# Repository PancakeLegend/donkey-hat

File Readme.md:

#CCHS dingo-hat

This is the readme.
---

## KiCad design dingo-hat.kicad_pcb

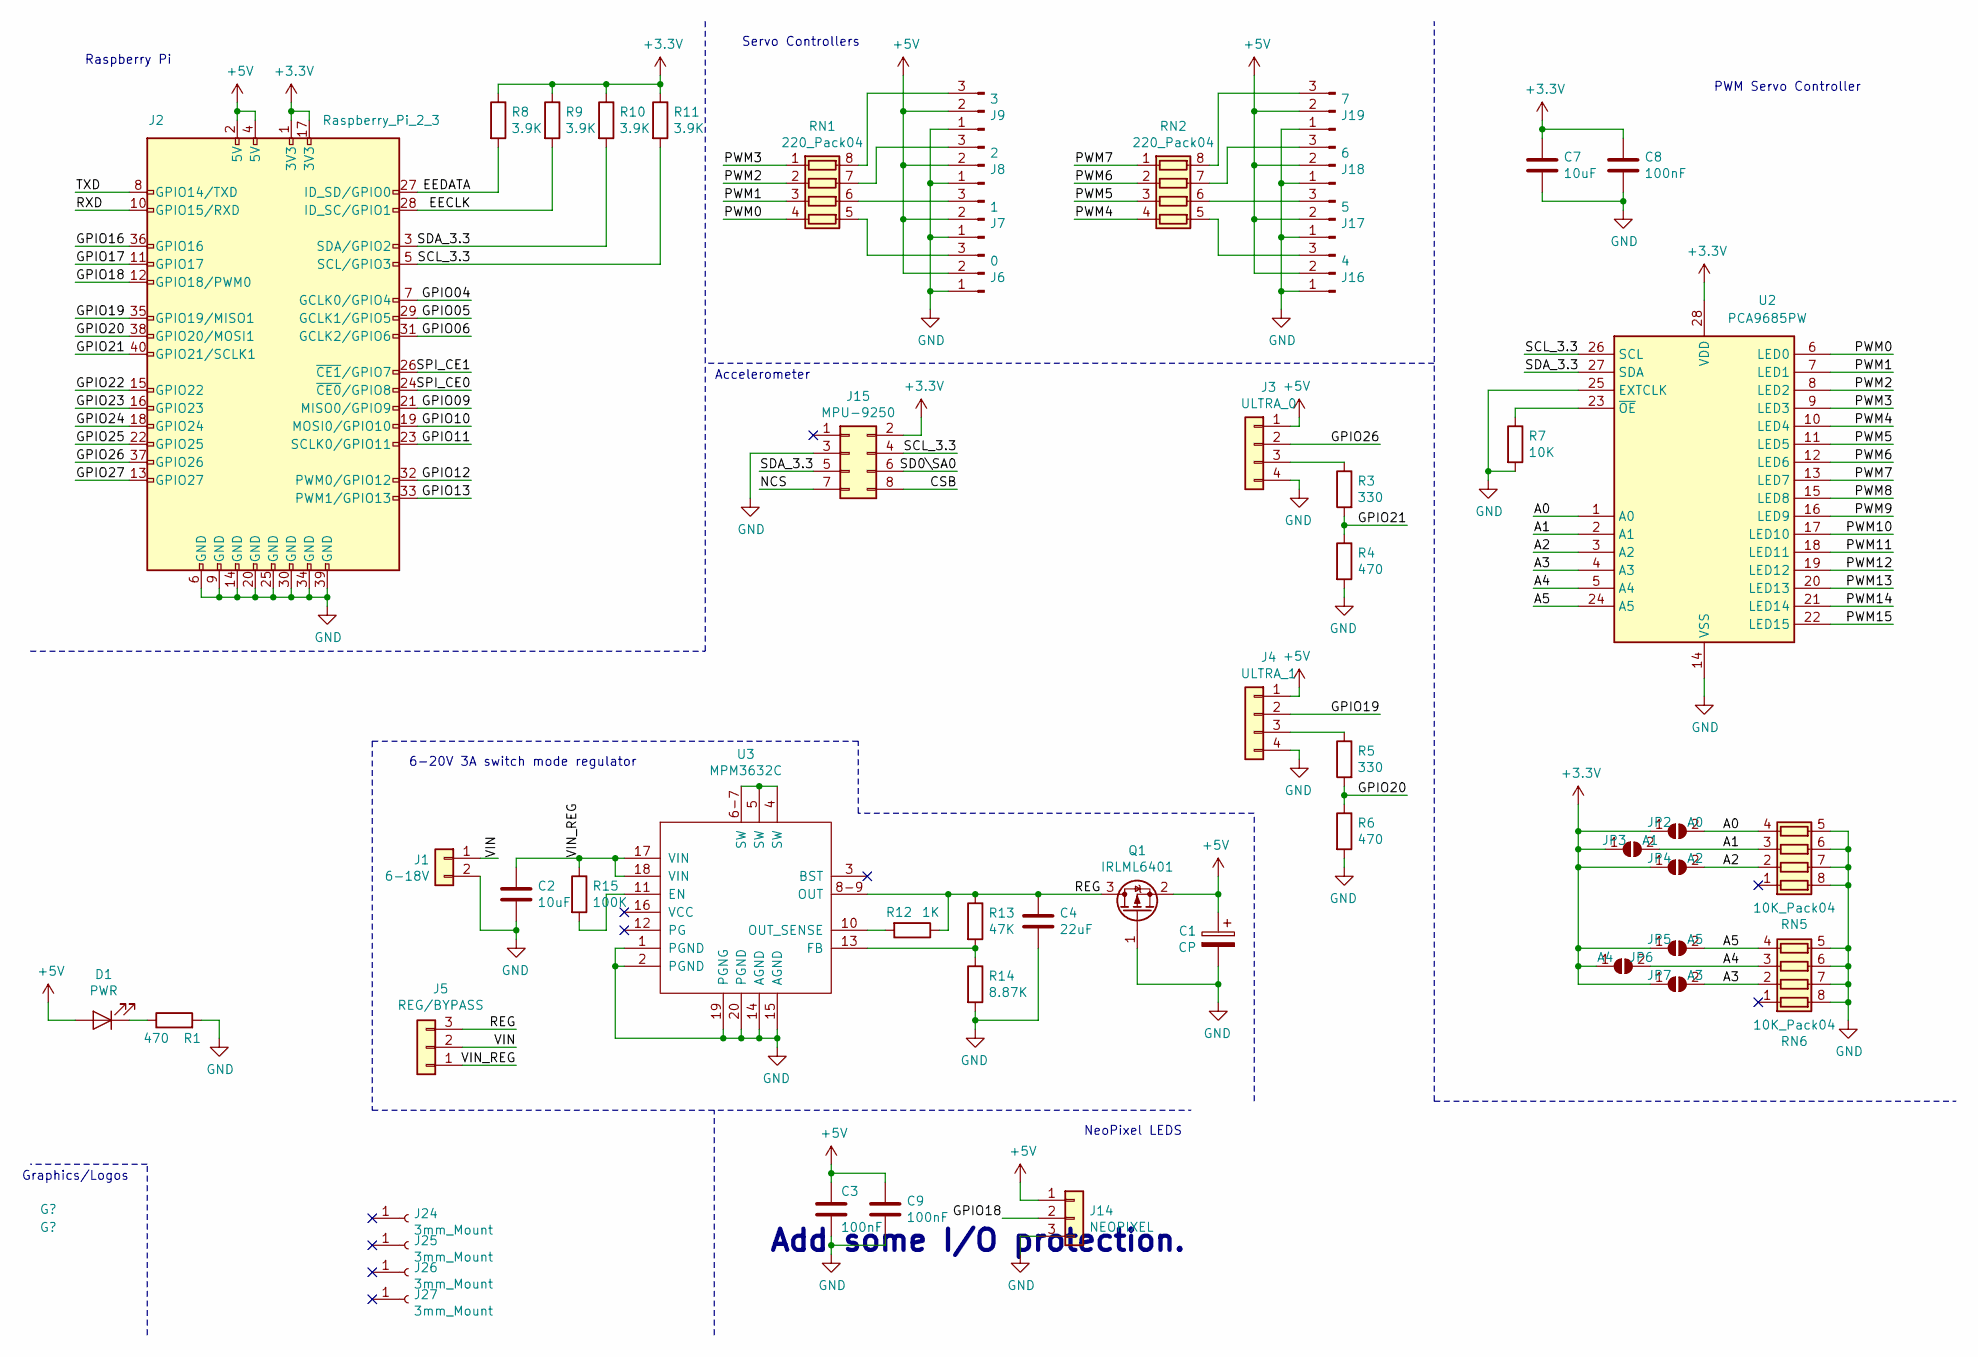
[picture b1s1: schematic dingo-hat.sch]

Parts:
C1: CP; CP_Radial_D5.0mm_P2.50mm
C2: 10uF; C_1206_3216Metric_Pad1.42x1.75mm_HandSolder
C3, C8, C9: 100nF; C_0603_1608Metric_Pad1.05x0.95mm_HandSolder
C4: 22uF; C_1206_3216Metric_Pad1.42x1.75mm_HandSolder
C7: 10uF; C_0603_1608Metric_Pad1.05x0.95mm_HandSolder
D1: PWR; LED_0603_1608Metric_Pad1.05x0.95mm_HandSolder
J1: 6-18V; PhoenixContact_MC_1,5_2-G-3.5_1x02_P3.50mm_Horizontal
J2: Raspberry_Pi_2_3; PinSocket_2x20_P2.54mm_Vertical
J3: ULTRA_0; PinSocket_1x04_P2.54mm_Vertical
J4: ULTRA_1; PinSocket_1x04_P2.54mm_Vertical
J5: REG/BYPASS; PinHeader_1x03_P2.54mm_Vertical
J6: 0; PinHeader_1x03_P2.54mm_Vertical
J7: 1; PinHeader_1x03_P2.54mm_Vertical
J8: 2; PinHeader_1x03_P2.54mm_Vertical
J9: 3; PinHeader_1x03_P2.54mm_Vertical
J14: NEOPIXEL; PinHeader_1x03_P2.54mm_Vertical
J15: MPU-9250; PinHeader_1x08_P2.54mm_Vertical
J16: 4; PinHeader_1x03_P2.54mm_Vertical
J17: 5; PinHeader_1x03_P2.54mm_Vertical
J18: 6; PinHeader_1x03_P2.54mm_Vertical
J19: 7; PinHeader_1x03_P2.54mm_Vertical
J24, J25, J26, J27: 3mm_Mount; MountingHole_3.2mm_M3
JP2: A0; SolderJumper-2_P1.3mm_Open_RoundedPad1.0x1.5mm
JP3: A1; SolderJumper-2_P1.3mm_Open_RoundedPad1.0x1.5mm
JP4: A2; SolderJumper-2_P1.3mm_Open_RoundedPad1.0x1.5mm
JP5: A5; SolderJumper-2_P1.3mm_Open_RoundedPad1.0x1.5mm
JP6: A4; SolderJumper-2_P1.3mm_Open_RoundedPad1.0x1.5mm
JP7: A3; SolderJumper-2_P1.3mm_Open_RoundedPad1.0x1.5mm
Q1: IRLML6401; SOT-23_Handsoldering; Mfg Part # IRLML6402PbF
R1, R4, R6: 470; R_0603_1608Metric_Pad1.05x0.95mm_HandSolder
R3, R5: 330; R_0603_1608Metric_Pad1.05x0.95mm_HandSolder
R7: 10K; R_0603_1608Metric_Pad1.05x0.95mm_HandSolder
R8, R9, R10, R11: 3.9K; R_0603_1608Metric_Pad1.05x0.95mm_HandSolder
R12: 1K; R_0603_1608Metric_Pad1.05x0.95mm_HandSolder
R13: 47K; R_0603_1608Metric_Pad1.05x0.95mm_HandSolder
R14: 8.87K; R_0603_1608Metric_Pad1.05x0.95mm_HandSolder
R15: 100K; R_0603_1608Metric_Pad1.05x0.95mm_HandSolder
RN1, RN2: 220_Pack04; R_Array_Convex_4x0603
RN5, RN6: 10K_Pack04; R_Array_Convex_4x0603
U2: PCA9685PW; TSSOP-28_4.4x9.7mm_P0.65mm; Mfg Part # PCA9685
U3: MPM3632C; mpm3632c; Mfg Part # MPM3632C

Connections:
+3V3: C7.1, C8.1, J2.1 (3V3), J2.17 (3V3), J15.2, JP2.1 (A), JP3.1 (A), JP4.1 (A), JP5.1 (A), JP6.1 (A), JP7.1 (A), R8.1, R9.1, R10.1, R11.1, U2.28 (VDD)
+5V: C1.1, C3.1, C9.1, D1.2 (A), J2.2 (5V), J2.4 (5V), J3.1, J4.1, J6.2, J7.2, J8.2, J9.2, J14.1, J16.2, J17.2, J18.2, J19.2, Q1.2 (S)
/A0: JP2.2 (B), RN5.4 (R4.1), U2.1 (A0)
/A1: JP3.2 (B), RN5.3 (R3.1), U2.2 (A1)
/A2: JP4.2 (B), RN5.2 (R2.1), U2.3 (A2)
/A3: JP7.2 (B), RN6.2 (R2.1), U2.4 (A3)
/A4: JP6.2 (B), RN6.3 (R3.1), U2.5 (A4)
/A5: JP5.2 (B), RN6.4 (R4.1), U2.24 (A5)
/CSB: J15.8
/EECLK: J2.28 (ID_SC/GPIO1), R9.2
/EEDATA: J2.27 (ID_SD/GPIO0), R8.2
/GPIO04: J2.7 (GCLK0/GPIO4)
/GPIO05: J2.29 (GCLK1/GPIO5)
/GPIO06: J2.31 (GCLK2/GPIO6)
/GPIO09: J2.21 (MISO0/GPIO9)
/GPIO10: J2.19 (MOSI0/GPIO10)
/GPIO11: J2.23 (SCLK0/GPIO11)
/GPIO12: J2.32 (PWM0/GPIO12)
/GPIO13: J2.33 (PWM1/GPIO13)
/GPIO16: J2.36 (GPIO16)
/GPIO17: J2.11 (GPIO17)
/GPIO18: J2.12 (GPIO18/PWM0), J14.2
/GPIO19: J2.35 (GPIO19/MISO1), J4.2
/GPIO20: J2.38 (GPIO20/MOSI1), R5.2, R6.1
/GPIO21: J2.40 (GPIO21/SCLK1), R3.2, R4.1
/GPIO22: J2.15 (GPIO22)
/GPIO23: J2.16 (GPIO23)
/GPIO24: J2.18 (GPIO24)
/GPIO25: J2.22 (GPIO25)
/GPIO26: J2.37 (GPIO26), J3.2
/GPIO27: J2.13 (GPIO27)
/NCS: J15.7
/PWM0: RN1.4 (R4.1), U2.6 (LED0)
/PWM1: RN1.3 (R3.1), U2.7 (LED1)
/PWM2: RN1.2 (R2.1), U2.8 (LED2)
/PWM3: RN1.1 (R1.1), U2.9 (LED3)
/PWM4: RN2.4 (R4.1), U2.10 (LED4)
/PWM5: RN2.3 (R3.1), U2.11 (LED5)
/PWM6: RN2.2 (R2.1), U2.12 (LED6)
/PWM7: RN2.1 (R1.1), U2.13 (LED7)
/PWM8: U2.15 (LED8)
/PWM9: U2.16 (LED9)
/PWM10: U2.17 (LED10)
/PWM11: U2.18 (LED11)
/PWM12: U2.19 (LED12)
/PWM13: U2.20 (LED13)
/PWM14: U2.21 (LED14)
/PWM15: U2.22 (LED15)
/REG: C4.1, J5.3, Q1.3 (D), R12.1, R13.1, U3.8-9 (OUT)
/RXD: J2.10 (GPIO15/RXD)
/SCL_3.3: J2.5 (SCL/GPIO3), J15.4, R11.2, U2.26 (SCL)
/SD0\SA0: J15.6
/SDA_3.3: J2.3 (SDA/GPIO2), J15.5, R10.2, U2.27 (SDA)
/SPI_CE0: J2.24 (~CE0~/GPIO8)
/SPI_CE1: J2.26 (~CE1~/GPIO7)
/TXD: J2.8 (GPIO14/TXD)
/VIN: J1.1, J5.2
/VIN_REG: C2.1, J5.1, R15.1, U3.17 (VIN), U3.18 (VIN)
GND: C1.2, C2.2, C3.2, C4.2, C7.2, C8.2, C9.2, J1.2, J2.6 (GND), J2.9 (GND), J2.14 (GND), J2.20 (GND), J2.25 (GND), J2.30 (GND), J2.34 (GND), J2.39 (GND), J3.4, J4.4, J6.1, J7.1, J8.1, J9.1, J14.3, J15.3, J16.1, J17.1, J18.1, J19.1, Q1.1 (G), R1.2, R4.2, R6.2, R7.2, R14.2, RN5.5 (R4.2), RN5.6 (R3.2), RN5.7 (R2.2), RN5.8 (R1.2), RN6.5 (R4.2), RN6.6 (R3.2), RN6.7 (R2.2), RN6.8 (R1.2), U2.14 (VSS), U2.25 (EXTCLK), U3.1 (PGND), U3.2 (PGND), U3.14 (AGND), U3.15 (AGND), U3.19 (PGNG), U3.20 (PGND)
unnamed: D1.1 (K), R1.1
unnamed: J3.3, R3.1
unnamed: J4.3, R5.1
unnamed: J6.3, RN1.5 (R4.2)
unnamed: J7.3, RN1.6 (R3.2)
unnamed: J8.3, RN1.7 (R2.2)
unnamed: J9.3, RN1.8 (R1.2)
unnamed: J16.3, RN2.5 (R4.2)
unnamed: J17.3, RN2.6 (R3.2)
unnamed: J18.3, RN2.7 (R2.2)
unnamed: J19.3, RN2.8 (R1.2)
unnamed: R7.1, U2.23 (~OE)
unnamed: R12.2, U3.10 (OUT_SENSE)
unnamed: R13.2, R14.1, U3.13 (FB)
unnamed: R15.2, U3.11 (EN)
unnamed: U3.4 (SW), U3.5 (SW), U3.6-7 (SW)

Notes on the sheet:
PWM Servo Controller
NeoPixel LEDS
Servo Controllers
Raspberry Pi
Accelerometer
6-20V 3A switch mode regulator
Add some I/O protection.
Graphics/Logos

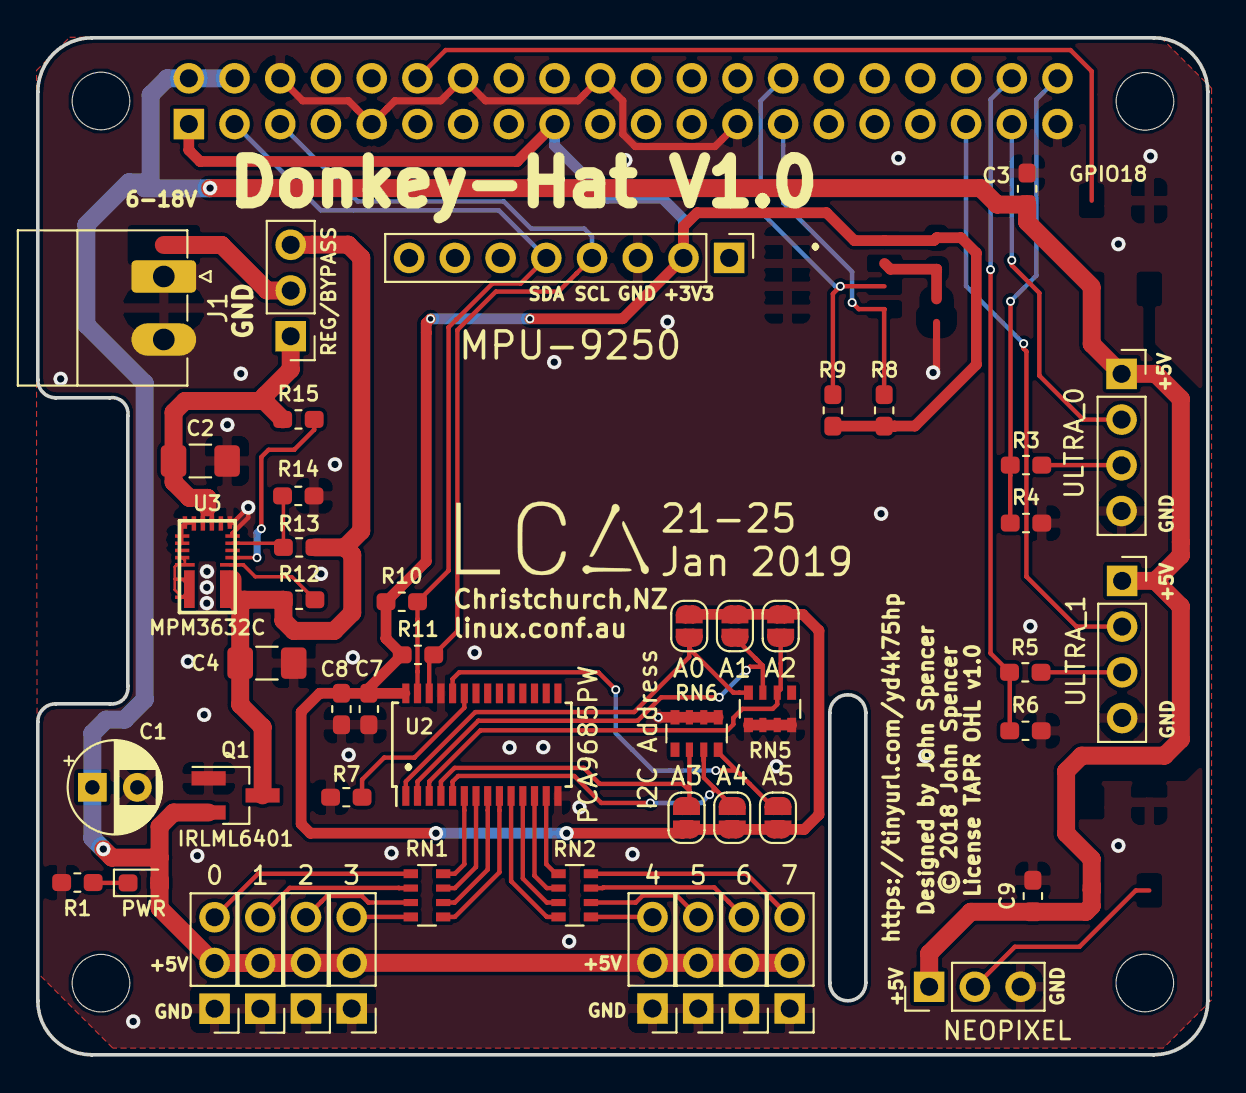
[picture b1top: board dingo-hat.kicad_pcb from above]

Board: 2 copper layers, 65.0 x 56.5 mm, 54 parts (1 on the bottom side), 45 nets.

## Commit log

2018-12-04 :octocat: Added .gitattributes & .gitignore files
2018-12-04 Initial push of the Donkey Hat
2018-12-04 Added logo and text.
2018-12-05 Flipped 5v in to stop breaking @projectgus
2018-12-05 Updated Schematic PDF
2018-12-05 Schematic updated
    PWM pins reduced.
    level shifter removed.
    Ultrasonic model changed.
2018-12-05 Resistor Bank for i2c is causing issues.
2018-12-05 New PCB to take in to account schematic changes
2018-12-05 Updated Images
2018-12-07 Added 5v regulator
2018-12-10 Updated to 0.3mm Vias.
    Makes pcbway a lot cheaper to order from.
2018-12-10 Many via replacements later
2018-12-12 Adding component footprints
2018-12-19 Added Regulator Bypass.
2018-12-22 Added logos and call outs.
2019-01-10 Minor trace and silkscreen updates
2019-01-14 Ignore Excel spreadsheets used for ordering.
2019-10-08 dingo-hat branch.
2019-10-08 Checking libs, project paths.
2019-10-09 Remove ws2812. Keep header.
2019-10-09 Touch readme.
2019-10-09 RM EEPROM.
2019-10-10 Rename 's/donkey/dingo/g'
2019-10-10 Adding schematic library for graphics/logos.
2019-10-14 Edge.Cuts and Dwgs.User reference layers
    Raspberry Pi have made DXFs available of their boards.
    https://www.raspberrypi.org/documentation/hardware/raspberrypi/mechanical/README.md
    The Pi 4 layout is aligned to a 0.05mm grid.
    Edge.Cuts and Dwgs.User DXFs (the latter includes the headers and mount hole positions) made directly from official Pi drawings. When importing into KiCAD, insert at 0,0 for accurate alignment.

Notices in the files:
dingo-hat.kicad_pcb:
© 2018 John Spencer
